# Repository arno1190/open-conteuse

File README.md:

# Galia

Two current custom handheld designs and an original bilingual listening collection. **Engineering RFQ release: physical validation and integrated audio firmware remain pending. No hardware is offered for sale.**

- **Galia Mini (contact ID):** 65 × 95 × 24 mm; a keyed cartridge selects audio stored inside the player, with an adult-replaceable picture behind a clear window. Passive DS2401 serial ID, two wear contacts, no NFC or audio on the card. Cartridge protrudes 20 mm when seated.
- **Galia Explore:** 67 × 95 × 24 mm, 2.4-inch display and button navigation. USB-C charging/data and 3.5 mm headphones on both.
- **Parent studio:** existing local import, exact-revision approval, card assignment and export foundation. Never deployed publicly.

[French showcase](https://arno1190.github.io/open-conteuse/?lang=fr) · [English showcase](https://arno1190.github.io/open-conteuse/?lang=en) · [RFQ launch playbook](rfq/LAUNCH-PLAYBOOK.md) · [RFQ scope](rfq/README.md) · [Design/assembly dossier](docs/design/README.md)

The intended differentiator is parent-controlled, highly personal listening made with their chosen tools and authorised sources. [MCP and provider/TTS connections remain under assessment](docs/PERSONALIZATION.md); no subscription/API compatibility is claimed. [Control UX and tactile-cap design](docs/design/UX.md) define the current refinement.

## Stories and cards

[Three original bilingual adventures](content/starter/README.md), [printable cards](content/starter/cards.pdf), [read-aloud booklet](content/starter/collection.pdf). Paper artwork does not activate the electronic reader. Scripts are editorial drafts; downloadable synthetic recordings and browser fallback are demonstrations, not approved final audio.

## Sources and checks

[Native KiCad](hardware/) · [OpenSCAD and prototype print meshes](enclosure/) · [BOM/cost assumptions](rfq/costs.json) · [Firmware](firmware/README.md) · [Independent audit](docs/AUDIT.md) · [Validation](docs/VALIDATION.md) · [Roadmap](docs/ROADMAP.md)

```sh
npm ci --ignore-scripts
sh scripts/check.sh
sh scripts/cad-check.sh
PIO=pio sh scripts/firmware-check.sh
python3 -m conteuse.studio --root .studio
```

Python host has no runtime dependencies. KiCad 9, OpenSCAD and PlatformIO are separate CAD/build requirements. The studio binds loopback and prints a per-launch token. Current firmware diagnostics keep audio muted; codec playback, hardware transfer and physical validation are unfinished.

Only the current designs are kept on main; earlier iterations remain in Git history. Original host/CAD/docs MIT; firmware GPL-3.0-or-later; original starter stories/art CC0-1.0. Dependencies retain upstream licences. No proprietary story libraries are included.

[Card exploded view and Wi-Fi administration](docs/design/CARDS.md): source-implemented parent setup/transfer/assignment and replaceable printed pictures; physical device and audio playback qualification remain pending.

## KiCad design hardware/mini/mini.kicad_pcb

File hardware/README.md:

# Current hardware

Only current RFQ designs are present. Open each folder's same-name .kicad_pro in KiCad9. All dimensions are nominal; physical validation pending.

- mini/:65×95×24mm contact-ID player main board,4layers60×83×1.2mm.
- explore/:67×95×24mm display player main board, same board envelope.
- card-reader/:50×11×1.6mm, protected single-drop1-Wire reader,2layers.
- story-card/:20×12×0.8mm DS2401P+ passive ROM token,2layers, selective hardgold wear pads.

Every folder includes exact-identity/reference BOM with source and search link, native schematic/PCB, parts data and actual checks. Drawing-defined parts still require supplier approval. [Dossier/assembly](../docs/design/README.md), [electrical notes](../docs/design/ELECTRICAL.md), [RFQ](../rfq/README.md).

Native KiCad upstream footprint geometry retains its library licence/exception; see LICENSES.md in board folders. Generated original CAD is MIT. No fabrication approval is implied.

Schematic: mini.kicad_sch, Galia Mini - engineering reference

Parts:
C1, C2, C3, C7, C16, C20, C26, C29: GRM21BR61A106KE19L; C_0805_2012Metric
C4, C5, C6: GRM21BR61A226ME44L; C_0805_2012Metric
C8, C11, C12, C13, C14, C15, C19, C21, C22, C23, C25, C30: GRM188R71C104KA01D; C_0603_1608Metric
C9, C10, C24: GRM188R61A105KA61D; C_0603_1608Metric
C17, C18: GRM32ER60J107ME20L; C_1210_3225Metric
D1: LTST-C190KGKT; LED_0603_1608Metric
H1, H2, H3, H4: M2; MountingHole_2.2mm_M2
J1: USB4105-GF-A; USB_C_Receptacle_GCT_USB4105-xx-A_16P_TopMnt_Horizontal
J2: DM3D-SF; microSD_HC_Hirose_DM3D-SF
J3: SJ-43514-SMT-TR; SJ43514
J4, J5, J6: S2B-PH-SM4-TB; JST_PH_S2B-PH-SM4-TB_1x02-1MP_P2.00mm_Horizontal
J7: BM07B-SRSS-TB; JST_SH_BM07B-SRSS-TB_1x07-1MP_P1.00mm_Vertical
L1: XFL4020-152MEC; L_Coilcraft_XxL4020
Q1: MMBT3904LT1G; SOT-23
R1: RC0603FR-071K78L; R_0603_1608Metric
R2: RC0603FR-073K57L; R_0603_1608Metric
R3: RC0603FR-073K01L; R_0603_1608Metric
R4, R7, R10, R13: RC0603FR-07100KL; R_0603_1608Metric
R5, R14, R15: RC0603FR-072K2L; R_0603_1608Metric
R6, R8, R9, R11, R16, R17, R22, R25, R26, R30, R31, R32, R33, R34, R35, R36, R37: RC0603FR-0710KL; R_0603_1608Metric
R12: RC0603FR-0720KL; R_0603_1608Metric
R18, R19: RC0603FR-075K1L; R_0603_1608Metric
R20, R21: RC0603FR-0727RL; R_0603_1608Metric
R23: RC0603JR-070RL; R_0603_1608Metric
R24: RC0603FR-071KL; R_0603_1608Metric
R45: RT0603BRD071ML; R_0603_1608Metric
R46: RT0603BRD07187KL; R_0603_1608Metric
SW1, SW2, SW3, SW4, SW5, SW10, SW11: KMR221GLFS; SW_Push_1P1T_NO_CK_KMR2
SW9: JS102011SAQN; SW_SPDT_CK_JS102011SAQN
TP1: GND; TestPoint_Pad_D1.0mm
TP2: 3V2; TestPoint_Pad_D1.0mm
TP3: UART_TX; TestPoint_Pad_D1.0mm
TP4: UART_RX; TestPoint_Pad_D1.0mm
TP5: MUTED; TestPoint_Pad_D1.0mm
TP6: IO6; TestPoint_Pad_D1.0mm
TP7: IO7; TestPoint_Pad_D1.0mm
TP8: SYS; TestPoint_Pad_D1.0mm
TP9: BAT; TestPoint_Pad_D1.0mm
TP10: 1V8; TestPoint_Pad_D1.0mm
U1: ESP32-S3-WROOM-1-N16R8; ESP32-S3-WROOM-1-R1
U2: BQ24074RGTR; VQFN-16-1EP_3x3mm_P0.5mm_EP1.6x1.6mm
U3: TPS63020DSJR; TPS63020_DSJ
U4: TLV75518PDBVR; SOT-23-5
U5: TLV320DAC3100IRHBR; Texas_RHB0032E_VQFN-32-1EP_5x5mm_P0.5mm_EP3.45x3.45mm
U6: SN74LVC1G74DCUR; VSSOP-8_2.3x2mm_P0.5mm
U7: SN74LVC1G08DBVR; SOT-23-5
U8: MAX98357AETE+T; TQFN-16-1EP_3x3mm_P0.5mm_EP1.23x1.23mm
U9: TCA9534PWR; TSSOP-16_4.4x5mm_P0.65mm
U10: USBLC6-2SC6; SOT-23-6

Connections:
/1V8: C10.1, C11.1, TP10.1, U4.5 (OUT), U5.3 (DVDD)
/3V2: C4.1, C5.1, C6.1, C9.1, C12.1, C13.1, C14.1, C15.1, C16.1, C21.1, C22.1, C23.1, C25.1, C26.1, C29.1, C30.1, J2.4, J7.1, R8.1, R9.1, R14.1, R15.1, R16.1, R17.1, R22.1, R25.1, R26.1, R30.1, R31.1, R32.1, R33.1, R34.1, R35.1, R36.1, R37.1, R45.1, TP2.1, U1.2 (3V3), U3.4 (VOUT), U3.5 (VOUT), U4.1 (IN), U4.3 (EN), U5.2 (IOVDD), U5.17 (AVDD), U5.21 (SPKVDD), U5.24 (SPKVDD), U5.28 (HPVDD), U6.8 (VCC), U7.5 (VCC), U9.16 (VCC)
/AMP_GAIN: R13.1, U8.2 (GAIN_SLOT)
/AMP_SD: R11.2, R12.1, U8.4 (~SD_MODE)
/BAT: C3.1, J5.1, TP9.1, U2.2 (BAT), U2.3 (BAT)
/BOOT_N: R17.2, SW10.1, U1.27 (IO0)
/CC1: J1.A5, R18.1
/CC2: J1.B5, R19.1
/CELL_NTC: J6.1, U2.1 (TS)
/CHG_ILIM: R1.1, U2.12 (ILIM)
/CHG_ISET: R2.1, U2.16 (ISET)
/CHG_ITERM: R3.1, U2.15 (ITERM)
/CODEC_IRQ: R6.1, U1.23 (IO21), U5.32 (GPIO1)
/GND: C1.2, C2.2, C3.2, C4.2, C5.2, C6.2, C7.2, C8.2, C9.2, C10.2, C11.2, C12.2, C13.2, C14.2, C15.2, C16.2, C19.2, C20.2, C21.2, C22.2, C23.2, C24.2, C25.2, C26.2, C29.2, C30.2, J1.A1, J1.A12, J1.B1, J1.B12, J1.S1, J2.6, J2.9, J2.10, J2.11, J3.4 (RING2_GND), J5.2, J6.2, J7.2, Q1.2, R1.2, R2.2, R3.2, R4.2, R7.2, R10.2, R12.2, R18.2, R19.2, R24.2, R46.2, SW1.2, SW2.2, SW3.2, SW4.2, SW5.2, SW9.3, SW10.2, SW11.2, TP1.1, U1.1 (GND), U1.40 (GND), U1.41 (GND), U2.4 (~CE), U2.5 (EN2), U2.8 (VSS), U2.17 (VSS), U3.2 (GND), U3.15 (PGND_EP), U4.2 (GND), U5.1 (IOVSS), U5.8 (MCLK), U5.16 (AVSS), U5.18 (DVSS), U5.20 (SPKVSS), U5.25 (SPKVSS), U5.29 (HPVSS), U5.33 (EP), U6.1 (CLK), U6.2 (D), U6.4 (GND), U7.3 (GND), U8.3 (GND), U8.11 (GND), U8.15 (GND), U8.17 (PAD), U9.1 (A0), U9.2 (A1), U9.3 (A2), U9.8 (GND), U10.2 (GND)
/HPL: C17.1, U5.27 (HPL)
/HPR: C18.1, U5.30 (HPR)
/HP_L: C17.2, J3.2 (TIP_L)
/HP_R: C18.2, J3.3 (RING1_R)
/I2C_SCL: R15.2, U1.38 (IO2), U5.10 (SCL), U9.14 (SCL)
/I2C_SDA: R14.2, U1.39 (IO1), U5.9 (SDA), U9.15 (SDA)
/I2S_BCLK: U1.33 (IO40), U5.7 (BCLK), U8.16 (BCLK)
/I2S_DATA: U1.35 (IO42), U5.5 (DIN), U8.1 (DIN)
/I2S_LRCLK: U1.34 (IO41), U5.6 (WCLK), U8.14 (LRCLK)
/IO4: U1.4 (IO4), U5.31 (RESET_N)
/IO5: R9.2, U1.5 (IO5), U6.6 (CLR_N)
/IO6: R23.2, TP6.1, U1.6 (IO6)
/IO7: TP7.1, U1.7 (IO7)
/IO8: J7.6, R25.2, U1.12 (IO8)
/IRQ_BASE: Q1.1, R6.2, R7.1
/KEY_A: R31.2, SW2.1, U9.5 (P1)
/KEY_B: R35.2, U9.10 (P5)
/KEY_DOWN: R32.2, U9.6 (P2)
/KEY_LEFT: R33.2, SW1.1, U9.7 (P3)
/KEY_RIGHT: R34.2, SW3.1, U9.9 (P4)
/KEY_UP: R30.2, U9.4 (P0)
/KEY_VOL_DOWN: R36.2, SW4.1, U9.11 (P6)
/KEY_VOL_UP: R37.2, SW5.1, U9.12 (P7)
/LATCH_ALLOW: U6.3 (Q_N), U7.1 (A)
/LED_K: D1.1, R24.1
/LED_STATUS: D1.2, U1.25 (IO48)
/MCU_EN: C24.1, R16.2, SW11.1, U1.3 (EN)
/MICBIAS: R5.1, U5.12 (MICBIAS)
/MICDET: J3.1 (SLEEVE_MICDET), R5.2, U5.11 (VOL_MICDET)
/MUTED: R23.1, TP5.1, U6.5 (Q)
/MUTE_PRE_N: Q1.3, R8.2, U6.7 (PRE_N)
/PWR_EN: R4.1, SW9.2, U3.12 (EN)
/REG_FB: R45.2, R46.1, U3.3 (FB)
/SD_CS: J2.2, R22.2, U1.18 (IO10)
/SPI_MISO: J2.7, U1.21 (IO13)
/SPI_MOSI: J2.3, U1.19 (IO11)
/SPI_SCK: J2.5, U1.20 (IO12)
/SPK_GATE: R11.1, U7.4 (Y)
/SPK_N: J4.2, U8.10 (OUTN)
/SPK_P: J4.1, U8.9 (OUTP)
/SPK_REQUEST: R10.1, U1.24 (IO47), U7.2 (B)
/SW_L1: L1.1, U3.8 (L1), U3.9 (L1)
/SW_L2: L1.2, U3.6 (L2), U3.7 (L2)
/SYS: C2.1, C7.1, C19.1, C20.1, R13.2, SW9.1, TP8.1, U2.10 (OUT), U2.11 (OUT), U3.10 (VIN), U3.11 (VIN), U3.13 (PS_SYNC), U8.7 (VDD), U8.8 (VDD)
/UART_RX: TP4.1, U1.36 (RXD0)
/UART_TX: TP3.1, U1.37 (TXD0)
/USB_DN: R21.2, U1.13 (USB_D-)
/USB_DP: R20.2, U1.14 (USB_D+)
/USB_N: J1.A7, J1.B7, R21.1, U10.3 (IO2), U10.4 (IO2)
/USB_P: J1.A6, J1.B6, R20.1, U10.1 (IO1), U10.6 (IO1)
/VBUS: C1.1, J1.A4, J1.A9, J1.B4, J1.B9, U2.6 (EN1), U2.13 (IN), U10.5 (VBUS)
/VINA: C8.1, U3.1 (VINA_internal)

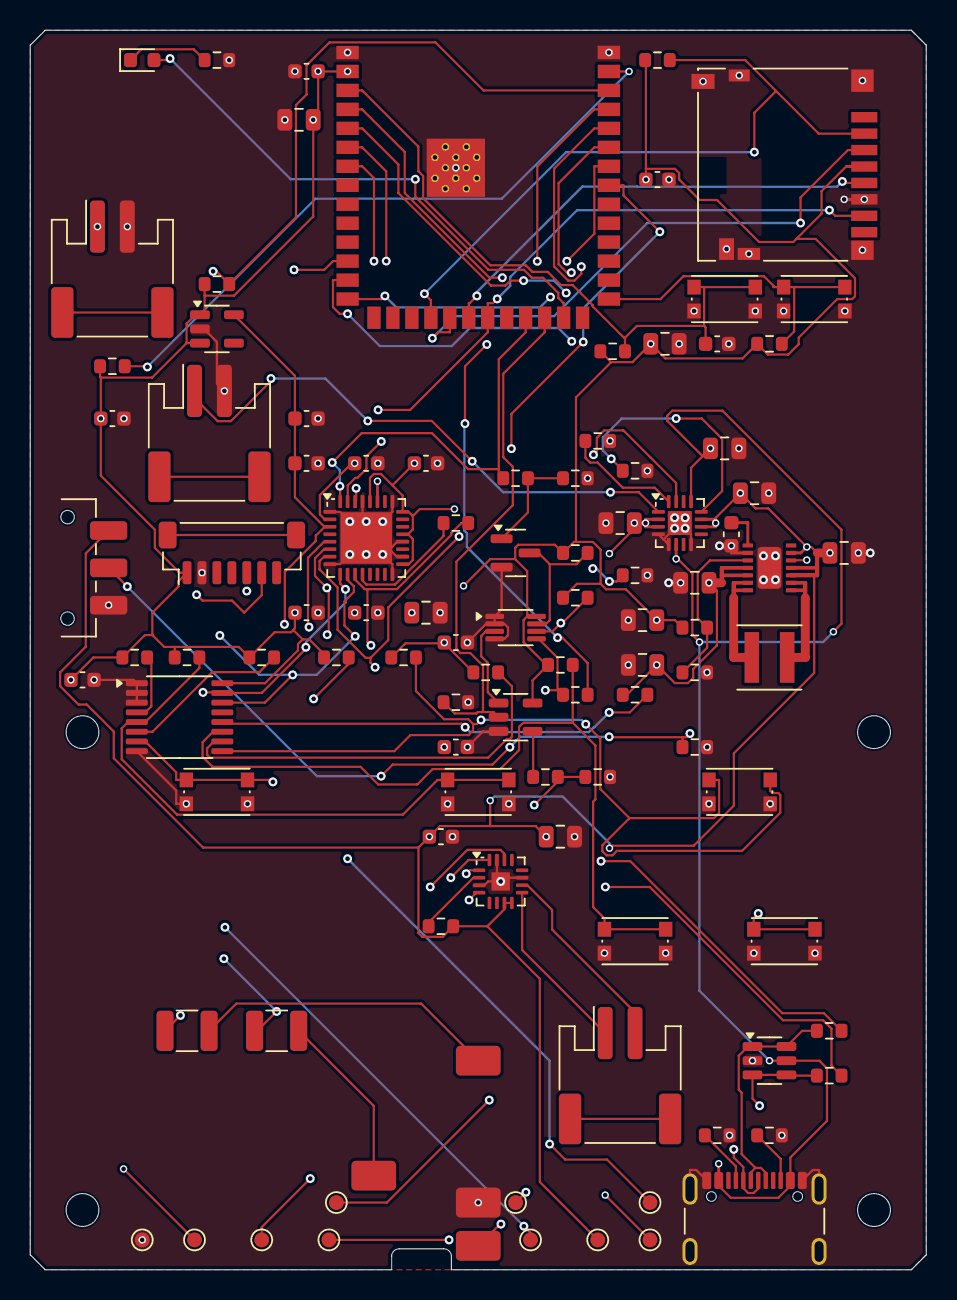
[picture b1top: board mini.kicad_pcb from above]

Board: 4 copper layers, 60.0 x 83.0 mm, 104 parts (0 on the bottom side), 66 nets.

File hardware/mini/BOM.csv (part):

reference,mpn,description,quantity,unit_eur_low,unit_eur_high,source,footprint,basis,search
U1,ESP32-S3-WROOM-1-N16R8,mcu,1,3.8,6.8,https://www.espressif.com/sites/default/files/documentation/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,Compact:ESP32-S3-WROOM-1-R1,planning allowance; not supplier quote,https://www.digikey.fr/en/products?keywords=ESP32-S3-WROOM-1-N16R8
U2,BQ24074RGTR,power,1,1.5,3,https://www.ti.com/lit/ds/symlink/bq24074.pdf,Package_DFN_QFN:VQFN-16-1EP_3x3mm_P0.5mm_EP1.6x1.6mm,planning allowance; not supplier quote,https://www.digikey.fr/en/products?keywords=BQ24074RGTR
R1,RC0603FR-071K78L,power,1,0.01,0.06,https://www.yageo.com/en/Product/Index/product_type/chip-resistors,Resistor_SMD:R_0603_1608Metric,planning allowance; not supplier quote,https://www.digikey.fr/en/products?keywords=RC0603FR-071K78L
R2,RC0603FR-073K57L,power,1,0.01,0.06,https://www.yageo.com/en/Product/Index/product_type/chip-resistors,Resistor_SMD:R_0603_1608Metric,planning allowance; not supplier quote,https://www.digikey.fr/en/products?keywords=RC0603FR-073K57L
R3,RC0603FR-073K01L,power,1,0.01,0.06,https://www.yageo.com/en/Product/Index/product_type/chip-resistors,Resistor_SMD:R_0603_1608Metric,planning allowance; not supplier quote,https://www.digikey.fr/en/products?keywords=RC0603FR-073K01L
C1,GRM21BR61A106KE19L,power,1,0.06,0.2,https://www.murata.com/en-global/products/capacitor/mlcc,Capacitor_SMD:C_0805_2012Metric,planning allowance; not supplier quote,https://www.digikey.fr/en/products?keywords=GRM21BR61A106KE19L
C2,GRM21BR61A106KE19L,power,1,0.06,0.2,https://www.murata.com/en-global/products/capacitor/mlcc,Capacitor_SMD:C_0805_2012Metric,planning allowance; not supplier quote,https://www.digikey.fr/en/products?keywords=GRM21BR61A106KE19L
C3,GRM21BR61A106KE19L,power,1,0.06,0.2,https://www.murata.com/en-global/products/capacitor/mlcc,Capacitor_SMD:C_0805_2012Metric,planning allowance; not supplier quote,https://www.digikey.fr/en/products?keywords=GRM21BR61A106KE19L
U3,TPS63020DSJR,power,1,2.2,4.5,https://www.ti.com/lit/ds/symlink/tps63020.pdf,Compact:TPS63020_DSJ,planning allowance; not supplier quote,https://www.digikey.fr/en/products?keywords=TPS63020DSJR
L1,XFL4020-152MEC,power,1,0.9,1.8,https://www.coilcraft.com/en-us/products/power/shielded-indu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,Inductor_SMD:L_Coilcraft_XxL4020,planning allowance; not supplier quote,https://www.digikey.fr/en/products?keywords=XFL4020-152MEC
C4,GRM21BR61A226ME44L,power,1,0.12,0.35,https://www.murata.com/en-global/products/capacitor/mlcc,Capacitor_SMD:C_0805_2012Metric,planning allowance; not supplier quote,https://www.digikey.fr/en/products?keywords=GRM21BR61A226ME44L
C5,GRM21BR61A226ME44L,power,1,0.12,0.35,https://www.murata.com/en-global/products/capacitor/mlcc,Capacitor_SMD:C_0805_2012Metric,planning allowance; not supplier quote,https://www.digikey.fr/en/products?keywords=GRM21BR61A226ME44L
C6,GRM21BR61A226ME44L,power,1,0.12,0.35,https://www.murata.com/en-global/products/capacitor/mlcc,Capacitor_SMD:C_0805_2012Metric,planning allowance; not supplier quote,https://www.digikey.fr/en/products?keywords=GRM21BR61A226ME44L
R45,RT0603BRD071ML,power,1,0.08,0.3,https://www.yageo.com/en/Product/Index/product_type/chip-resistors,Resistor_SMD:R_0603_1608Metric,planning allowance; not supplier quote,https://www.digikey.fr/en/products?keywords=RT0603BRD071ML
R46,RT0603BRD07187KL,power,1,0.08,0.3,https://www.yageo.com/en/Product/Index/product_type/chip-resistors,Resistor_SMD:R_0603_1608Metric,planning allowance; not supplier quote,https://www.digikey.fr/en/products?keywords=RT0603BRD07187KL
C7,GRM21BR61A106KE19L,power,1,0.06,0.2,https://www.murata.com/en-global/products/capacitor/mlcc,Capacitor_SMD:C_0805_2012Metric,planning allowance; not supplier quote,https://www.digikey.fr/en/products?keywords=GRM21BR61A106KE19L
C8,GRM188R71C104KA01D,power,1,0.02,0.08,https://www.murata.com/en-global/products/capacitor/mlcc,Capacitor_SMD:C_0603_1608Metric,planning allowance; not supplier quote,https://www.digikey.fr/en/products?keywords=GRM188R71C104KA01D
R4,RC0603FR-07100KL,power,1,0.01,0.06,https://www.yageo.com/en/Product/Index/product_type/chip-resistors,Resistor_SMD:R_0603_1608Metric,planning allowance; not supplier quote,https://www.digikey.fr/en/products?keywords=RC0603FR-07100KL
SW9,JS102011SAQN,power,1,0.5,1.5,https://www.ckswitches.com/media/1422/js.pdf,Button_Switch_SMD:SW_SPDT_CK_JS102011SAQN,planning allowance; not supplier quote,https://www.digikey.fr/en/products?keywords=JS102011SAQN
U4,TLV75518PDBVR,audio,1,0.2,0.7,https://www.ti.com/lit/ds/symlink/tlv755p.pdf,Package_TO_SOT_SMD:SOT-23-5,planning allowance; not supplier quote,https://www.digikey.fr/en/products?keywords=TLV75518PDBVR
C9,GRM188R61A105KA61D,audio,1,0.03,0.12,https://www.murata.com/en-global/products/capacitor/mlcc,Capacitor_SMD:C_0603_1608Metric,planning allowance; not supplier quote,https://www.digikey.fr/en/products?keywords=GRM188R61A105KA61D
C10,GRM188R61A105KA61D,audio,1,0.03,0.12,https://www.murata.com/en-global/products/capacitor/mlcc,Capacitor_SMD:C_0603_1608Metric,planning allowance; not supplier quote,https://www.digikey.fr/en/products?keywords=GRM188R61A105KA61D
U5,TLV320DAC3100IRHBR,audio,1,2,4,https://www.ti.com/lit/ds/symlink/tlv320dac3100.pdf,Package_DFN_QFN:Texas_RHB0032E_VQFN-32-1EP_5x5mm_P0.5mm_EP3.45x3.45mm,planning allowance; not supplier quote,https://www.digikey.fr/en/products?keywords=TLV320DAC3100IRHBR
C11,GRM188R71C104KA01D,audio,1,0.02,0.08,https://www.murata.com/en-global/products/capacitor/mlcc,Capacitor_SMD:C_0603_1608Metric,planning allowance; not supplier quote,https://www.digikey.fr/en/products?keywords=GRM188R71C104KA01D
C12,GRM188R71C104KA01D,audio,1,0.02,0.08,https://www.murata.com/en-global/products/capacitor/mlcc,Capacitor_SMD:C_0603_1608Metric,planning allowance; not supplier quote,https://www.digikey.fr/en/products?keywords=GRM188R71C104KA01D
C13,GRM188R71C104KA01D,audio,1,0.02,0.08,https://www.murata.com/en-global/products/capacitor/mlcc,Capacitor_SMD:C_0603_1608Metric,planning allowance; not supplier quote,https://www.digikey.fr/en/products?keywords=GRM188R71C104KA01D
C14,GRM188R71C104KA01D,audio,1,0.02,0.08,https://www.murata.com/en-global/products/capacitor/mlcc,Capacitor_SMD:C_0603_1608Metric,planning allowance; not supplier quote,https://www.digikey.fr/en/products?keywords=GRM188R71C104KA01D
C15,GRM188R71C104KA01D,audio,1,0.02,0.08,https://www.murata.com/en-global/products/capacitor/mlcc,Capacitor_SMD:C_0603_1608Metric,planning allowance; not supplier quote,https://www.digikey.fr/en/products?keywords=GRM188R71C104KA01D
C16,GRM21BR61A106KE19L,audio,1,0.06,0.2,https://www.murata.com/en-global/products/capacitor/mlcc,Capacitor_SMD:C_0805_2012Metric,planning allowance; not supplier quote,https://www.digikey.fr/en/products?keywords=GRM21BR61A106KE19L
R5,RC0603FR-072K2L,audio,1,0.01,0.06,https://www.yageo.com/en/Product/Index/product_type/chip-resistors,Resistor_SMD:R_0603_1608Metric,planning allowance; not supplier quote,https://www.digikey.fr/en/products?keywords=RC0603FR-072K2L
C17,GRM32ER60J107ME20L,audio,1,0.5,1.2,https://www.murata.com/en-global/products/capacitor/mlcc,Capacitor_SMD:C_1210_3225Metric,planning allowance; not supplier quote,https://www.digikey.fr/en/products?keywords=GRM32ER60J107ME20L
C18,GRM32ER60J107ME20L,audio,1,0.5,1.2,https://www.murata.com/en-global/products/capacitor/mlcc,Capacitor_SMD:C_1210_3225Metric,planning allowance; not supplier quote,https://www.digikey.fr/en/products?keywords=GRM32ER60J107ME20L
J3,SJ-43514-SMT-TR,audio,1,0.8,2,https://jp.sameskydevices.com/product/resource/sj-4351x-smt.pdf,Compact:SJ43514,planning allowance; not supplier quote,https://www.digikey.fr/en/products?keywords=SJ-43514-SMT-TR
U6,SN74LVC1G74DCUR,audio,1,0.25,0.7,https://www.ti.com/lit/ds/symlink/sn74lvc1g74.pdf,Package_SO:VSSOP-8_2.3x2mm_P0.5mm,planning allowance; not supplier quote,https://www.digikey.fr/en/products?keywords=SN74LVC1G74DCUR
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
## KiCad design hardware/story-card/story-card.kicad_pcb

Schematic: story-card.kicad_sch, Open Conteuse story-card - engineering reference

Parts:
H1, H2: M1.6; Mount_M1_6
J1: OC-ID-CONTACTS; ContactPads_Bottom
U1: DS2401P+; TSOC-6_3.76x3.94mm_P1.27mm

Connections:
/CARD_DQ: J1.2, U1.2 (DQ)
/GND: J1.1, U1.1 (GND)

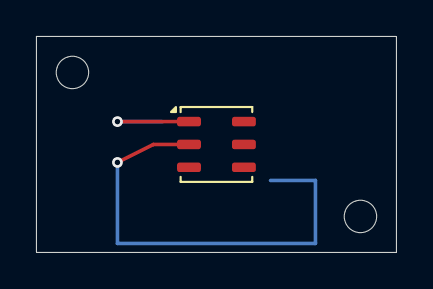
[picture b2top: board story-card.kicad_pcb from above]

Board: 2 copper layers, 20.0 x 12.0 mm, 4 parts (0 on the bottom side), 2 nets.

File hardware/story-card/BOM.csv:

reference,mpn,description,quantity,unit_eur_low,unit_eur_high,source,footprint,basis,search
U1,DS2401P+,card,1,3.65,5,https://www.analog.com/media/en/technical-documentation/data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,Package_SO_J-Lead:TSOC-6_3.76x3.94mm_P1.27mm,planning allowance; not supplier quote,https://www.digikey.fr/en/products?keywords=DS2401P%2B
J1,OC-ID-CONTACTS,card,1,0,0,selective hard-gold contact drawing; no audio storage,Compact:ContactPads_Bottom,planning allowance; not supplier quote,https://www.digikey.fr/en/products?keywords=OC-ID-CONTACTS
CASE,OC-ID-CARD-CASE,Two printed cartridge halves and label; no audio storage,1,0.5,2,enclosure/card.scad,external,engineering allowance; not a quote,https://www.google.com/search?q=OC-ID-CARD-CASE
SCR,ISO7045-Z-M1.6x3-A2,Two cartridge handle panhead screws,2,0.04,0.15,docs/design/README.md,external,engineering allowance; not a quote,https://www.google.com/search?q=ISO7045-Z-M1.6x3-A2
PCB,OC-ID-CARD-PCB,20x12x0.8mm 2layer selective hardgold wear pads; MOQ/NRE excluded,1,1,4,hardware/story-card/story-card.kicad_pcb,external,engineering allowance; not a quote,https://www.google.com/search?q=OC-ID-CARD-PCB

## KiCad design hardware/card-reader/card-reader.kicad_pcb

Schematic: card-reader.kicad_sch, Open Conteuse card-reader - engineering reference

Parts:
D1: TPD1E10B06DPYR; Texas_DPY0002A_0.6x1mm_P0.65mm
D2: BAT54S,215; SOT-23
H1, H2: M1.6; Mount_M1_6
J1: OC-WIRE-3; Wire3_Top
P1, P2: P70-1000045R; Pogo_P70_1000045
R1: RC0603FR-074K3L; R_0603_1608Metric
R2: RC0603FR-07330RL; R_0603_1608Metric

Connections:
/3V2: D2.2, J1.1, R1.1
/CARD_DQ: D1.1, P2.1, R2.2
/GND: D1.2, D2.1, J1.2, P1.1
/IO8: D2.3, J1.3, R1.2, R2.1

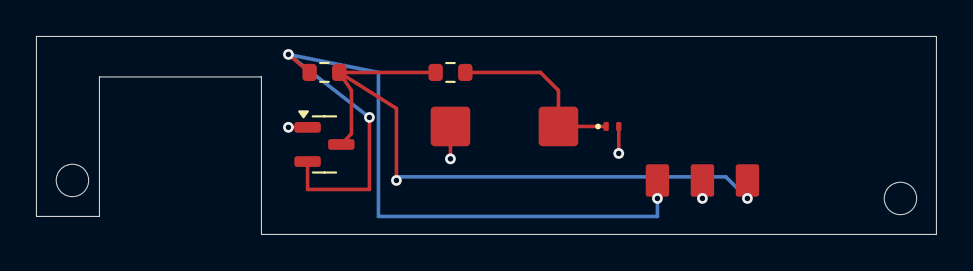
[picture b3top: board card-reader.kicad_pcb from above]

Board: 2 copper layers, 50.0 x 11.0 mm, 9 parts (0 on the bottom side), 4 nets.

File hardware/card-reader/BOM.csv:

reference,mpn,description,quantity,unit_eur_low,unit_eur_high,source,footprint,basis,search
J1,OC-WIRE-3,card,1,0,0,drawing-defined solder-wire termination,Compact:Wire3_Top,planning allowance; not supplier quote,https://www.digikey.fr/en/products?keywords=OC-WIRE-3
P1,P70-1000045R,card,1,0.8,1.8,https://www.harwin.com/products/P70-1000045R,Compact:Pogo_P70_1000045,planning allowance; not supplier quote,https://www.digikey.fr/en/products?keywords=P70-1000045R
P2,P70-1000045R,card,1,0.8,1.8,https://www.harwin.com/products/P70-1000045R,Compact:Pogo_P70_1000045,planning allowance; not supplier quote,https://www.digikey.fr/en/products?keywords=P70-1000045R
R1,RC0603FR-074K3L,card,1,0.01,0.06,https://www.yageo.com/en/Product/Index/product_type/chip-resistors,Resistor_SMD:R_0603_1608Metric,planning allowance; not supplier quote,https://www.digikey.fr/en/products?keywords=RC0603FR-074K3L
R2,RC0603FR-07330RL,card,1,0.01,0.06,https://www.yageo.com/en/Product/Index/product_type/chip-resistors,Resistor_SMD:R_0603_1608Metric,planning allowance; not supplier quote,https://www.digikey.fr/en/products?keywords=RC0603FR-07330RL
D1,TPD1E10B06DPYR,card,1,0.15,0.5,https://www.ti.com/lit/ds/symlink/tpd1e10b06.pdf,Package_SON:Texas_DPY0002A_0.6x1mm_P0.65mm,planning allowance; not supplier quote,https://www.digikey.fr/en/products?keywords=TPD1E10B06DPYR
D2,"BAT54S,215",card,1,0.05,0.2,https://assets.nexperia.com/documents/data-sheet/BAT54_SER.pdf,Package_TO_SOT_SMD:SOT-23,planning allowance; not supplier quote,https://www.digikey.fr/en/products?keywords=BAT54S%2C215
PCB,OC-ID-READER-PCB,50x11x1.6mm 2layer FR4 reader; MOQ/NRE excluded,1,1,3,hardware/card-reader/card-reader.kicad_pcb,external,engineering allowance; not a quote,https://www.google.com/search?q=OC-ID-READER-PCB

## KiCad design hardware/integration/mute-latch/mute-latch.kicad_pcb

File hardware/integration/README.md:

# Integrated modular prototype — revision 1

This is the detailed successor to the original bench envelope. The configuration is inspired by the owner's canteen project workflow: one catalogue, one placement file, sourcing queries on every BOM row, native CAD references and reproducible export checks. No private reference-project material is included.

**Status: nominal CAD prototype, not a physically validated or procurement-complete product.** Downloadable prototype STLs are in `../../enclosure/integrated/print/`. Do not substitute the historical `enclosure/shell.scad` for this enclosure. The integrated case is 112 × 210 × 50 mm. The Mini uses the actual long PN532 board; Explore omits NFC and uses the 2090 display.

## Sources and exact configuration

- [BOM.csv](BOM.csv): exact manufacturer/order identifiers, per-device quantities, observed supplier price/stock and DigiKey, Mouser and AliExpress search queries for **every** row. Search results are discovery links, not approved substitutes or authenticity guarantees.
- [catalog.json](catalog.json): dimensions, supplier CAD source URLs, Git object identities, source/derived hashes, mounting-hole coordinates, dimensional conflicts, quotes and assumptions.
- [layout.json](layout.json): all module poses, ports and removable-card/wire corridors in mm.
- [status.json](status.json): generated missing-quote/availability gates and minimum purchase-pack subtotals for one Mini plus one Explore.
- [mute-latch](mute-latch): native routed KiCad 9 schematic/PCB and local libraries for the independent insertion-mute latch. Existing controls PCB remains `../controls`.

Selected modules: Espressif ESP32-S3-DevKitC-1-N16R8 **PCB V1.1**; Adafruit 364 PN532 v1.6 (Mini), 2090 ILI9341 capacitive TFT (Explore; touch unused), 4682 microSD, 6309 TLV320DAC3100 headphone DAC, 3006 MAX98357A speaker amplifier, 6091 BQ25185 charger, 328 protected cell, 3351 enclosed speaker, 805 slide switch; Pololu 2873 regulated 3.3 V supply. Small-part MPNs are enumerated separately, rather than hiding them in an allowance.

No substitute board is dimensionally equivalent merely because it uses the same IC. PN532 manufacturer CAD is 120 × 50 mm whereas retail prose differs. The protected cell reservation combines the larger published dimension on each axis. The speaker uses the larger 19.7 mm CAD depth. ESP assembled/header height is a **14.5 mm reservation**, not a measured height. Switch STEP is an undetailed rectangular envelope: actuator location/slot and cradle require actual-part measurements. Neither uncertain item is represented as a detailed exact model.

## Electrical integration contract

Protected battery → BQ25185 BAT; charger LOAD → regulator VIN and MAX98357A VIN. Pololu fixed 3.3 V → MCU 3V3 and all logic modules; common GND. Charger retains factory 4.2 V / 1 A configuration (cell specified max charge 1.2 A). Slide switch pulls regulator EN to GND to sleep; never drive EN high. Raw LOAD remains powered when regulator sleeps; this is not a service isolation switch. Regulator typical near-battery output is 1.5 A, startup around 700 mA until regulation: delay Wi-Fi/heavy loads. Actual concurrent current, startup, thermal and brownout tests remain pending.

**Never connect MCU native USB/5V while it receives external 3V3.** Charging USB-C is charge-only. Service flashing requires disconnecting external power and confirming isolation; EN-off alone is insufficient. Do not attach charger/battery before polarity and short-circuit checks. Use the battery's manufacturer protection; the printed cage does not provide electrical protection.

Integrated wiring target (not yet implemented in firmware): buttons GPIO4/5/6/7/15/16/17/18; I²C SDA1/SCL2; PN532 IRQ8/RESET9; SD CS10/MOSI11/SCK12/MISO13; TFT CS14/DC48, RESET tied to ESP EN; I²S BCLK40/LRCLK41/DATA42; amplifier request47; latch Q21 and active-low CLR39. Reserve GPIO38 for DevKit V1.1 RGB, USB19/20, OPI35/36/37, boot straps0/3/45/46 and UART43/44. The old bench profile uses different GPIOs and lacks the TLV320 codec driver: **do not flash it onto this wiring**. Integrated firmware/codec bring-up is an explicit release gate.

Mute latch: TLV320 IO1 IRQ pulse drives 2N3904 through10k; base100k to GND; collector pulls HC74 PRE_N low (10k pullup). HC74 Q→GPIO21; /Q AND GPIO47 via HC08→amp SD. D/CLK grounded, CLR_N GPIO39 with10k pullup; all unused gate inputs tied, unused outputs NC. GPIO47 and SD each have10k pulldown; add the mandatory extra **local10k at amp SD/GND** so an unplugged harness leaves it muted. Both logic ICs use regulated3V3 and100nF decoupling. See schematic for header pin order; never infer order from this prose.

Boot holds GPIO47 LOW. Configure codec headset detection/internal oscillator and repeating IRQ, clear checked codec flags, clear latch with amplifier held LOW, release CLR, then perform checked no-headset/status and Q-low reads before enabling. I²C failure means muted. PRE and CLR simultaneous LOW can make both Q and /Q HIGH: never enable while clearing. This circuit latches insertion IRQ even if the loop stalls, but is not protection against codec reset, lost AVDD or broken IRQ. No physical headphone-mute safety result is claimed.

## Adult assembly and validation

1. Confirm every received PCB revision/MPN, battery polarity, exact connector and fastener geometry. Measure MCU assembled height, switch actuator, solder/header protrusions and actual plug barrels. Update catalogue/poses and rerun exports before a full case print.
2. Print the coupon first. Confirm M2.5 screw clearance, plain DIN934 nut capture and connector opening clearances. Nyloc nuts are taller and are not substitutes.
3. PETG baseline: 0.4 mm nozzle, 0.2 mm layers, ≥3 perimeters, 20–30% infill. These are starting settings, not validated strength. Slicer/orientation/support review is required; no printer-specific G-code is supplied. Front exterior faces the bed; all STL exports have nonnegative Z. Wide flat parts may need a brim; tall wall ledges may need support.
4. Install nuts into front pockets. Insert button stems **from inside**: the large internal head retains each cap. Fit controls PCB over them, then test free travel before wiring. Fit variant PCB and sealed speaker using the rigid4 mm PETG spacer; it is not an acoustic gasket.
5. Assemble removable carrier, modules, battery cage and cover. Use two MCU bars, one regulator bar and one switch bar. Route trimmed soldered harnesses with strain relief; avoid exposed plug-in jumpers. Leave SD extraction corridor clear. Do not overtighten against PCBs or pouch cell. Tie tension must close on the rigid cage, not compress the cell.
6. Verify service access and that lid/retainers cannot touch components or wires. Use M2.5×6 socket screws and plain2 mm-high nuts; selected mounting count43 pairs/device includes4 case,4 carrier,12 front,15 rear module,4 MCU,2 regulator,2 switch pairs. Verify screw engagement before tightening: supplier PCB stack variations require rechecking length.
7. Bench test isolated USB logic first with current limiting; then power rail startup/load, SD/NFC/TFT, codec/I²S and insertion mute. Finally battery/charge thermal, sound level, runtime, acoustic seal, NFC range, drop/retention and repeated assembly tests. Record results; all remain pending.

The render/export/mesh checks prove only properties of digital geometry. They do not establish electrical safety, child suitability, battery containment, mechanical strength or that every actual part fits. No purchases or fabrication orders were made.

## Reproduce

```sh
python3 scripts/integrated_hardware.py
python3 scripts/export_integrated.py
sh scripts/check.sh
sh scripts/cad-check.sh
sh scripts/firmware-check.sh
```

KiCad9 and OpenSCAD2021.01 are the checked CAD tool versions. Generator `scripts/generate_mute_latch.py` requires system Python with pcbnew. Preview rendering additionally uses the pinned numpy/matplotlib packages in `scripts/requirements-preview.txt`. The catalogue and geometric host checks need only Python standard library.

### Screw and solder clearance assumptions

M2.5×6 is measured under its head. For1.57/1.6mm modulePCBs, the tip lies4.43/4.4mm below the PCB support plane; global blind bores preserve a nominal0.6mm floor skin instead of being refilled by the case/carrier union. Speaker body is raised to6.4mm with a4mm spacer. Native CAD flange bearing surfaces are localZ1.0–2.7mm (1.7mm thick), so posts end at globalZ7.4 and screw tips atZ3.1. Verify the actual flange before assembly. Its post bores remain blind and nut cavities are open from the PCB side. Screw heads and tool approach still require received-part verification. Trim through-hole solder leads to≤2mm under every3mm PCB standoff; do not leave long header tails to touch the carrier. Bare standoffs do not provide insulation for unknown protruding components.

CAD poses use bare module assemblies without optional tall pin headers or the MAX98357A screw-terminal block. Solder the strain-relieved speaker lead directly to the amplifier output pads; do not add an unmodelled terminal block. Battery's included matching JST-PH lead connects to charger BAT; retain its protection and verify polarity. Any added plug/socket, terminal block or replacement speaker lead requires an exact BOM row, envelope and revised fit check. Latch's specified Samtec headers are included in its10mm upper reservation and still require received-part/lead-trim checks.

## Full visual atlas

The [combined visual design document](../../docs/visual-atlas) includes exterior/orthographic, exploded, sectional, module and service views for Mini and Explore, with a downloadable PDF. Its orange faces show sections of the supplied CAD solids; they do not reveal hidden speaker/cell construction. Shared-module close-ups are grouped with Mini; Explore adds its display and eight-switch controls view. Visual proxies and generic component bodies are labelled and do not replace received-part measurements.

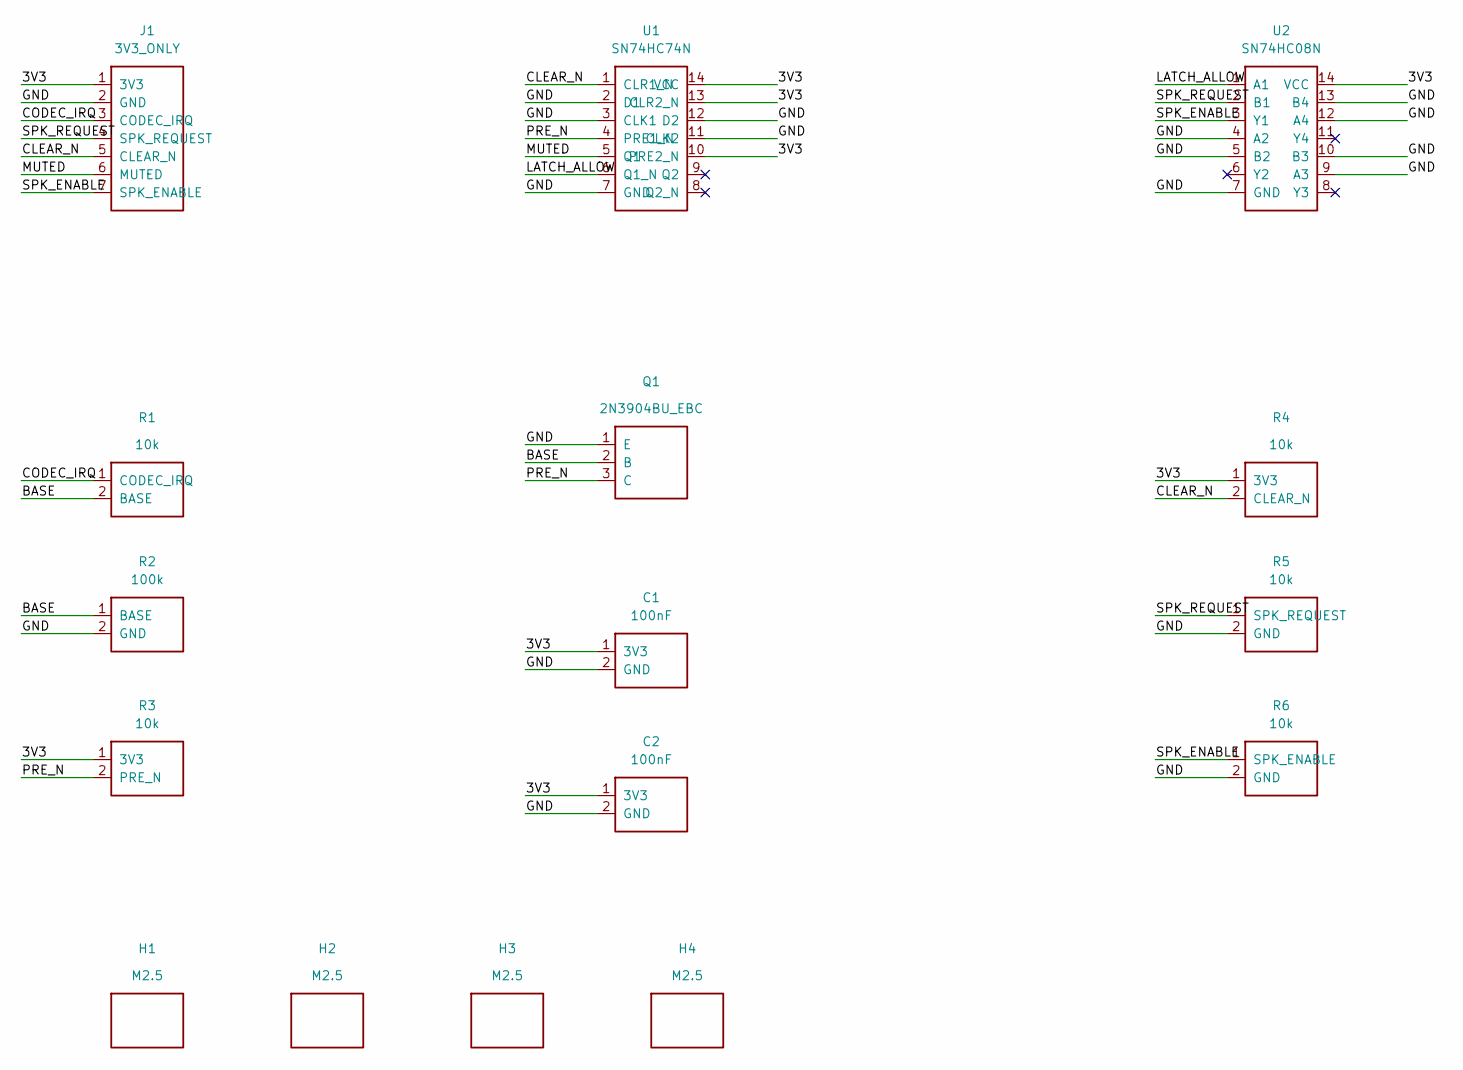
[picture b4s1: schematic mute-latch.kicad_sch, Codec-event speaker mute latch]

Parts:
C1, C2: 100nF; C_Disc_D5.0mm_W2.5mm_P2.54mm
H1, H2, H3, H4: M2.5; MountingHole_2.7mm_M2.5
J1: 3V3_ONLY; PinHeader_1x07_P2.54mm_Vertical
Q1: 2N3904BU_EBC; TO-92_Inline
R1, R3, R4, R5, R6: 10k; R_Axial_DIN0207_L6.3mm_D2.5mm_P7.62mm_Horizontal
R2: 100k; R_Axial_DIN0207_L6.3mm_D2.5mm_P7.62mm_Horizontal
U1: SN74HC74N; DIP-14_W7.62mm
U2: SN74HC08N; DIP-14_W7.62mm

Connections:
/3V3: C1.1 (3V3), C2.1 (3V3), J1.1 (3V3), R3.1 (3V3), R4.1 (3V3), U1.10 (PRE2_N), U1.13 (CLR2_N), U1.14 (VCC), U2.14 (VCC)
/BASE: Q1.2 (B), R1.2 (BASE), R2.1 (BASE)
/CLEAR_N: J1.5 (CLEAR_N), R4.2 (CLEAR_N), U1.1 (CLR1_N)
/CODEC_IRQ: J1.3 (CODEC_IRQ), R1.1 (CODEC_IRQ)
/GND: C1.2 (GND), C2.2 (GND), J1.2 (GND), Q1.1 (E), R2.2 (GND), R5.2 (GND), R6.2 (GND), U1.2 (D1), U1.3 (CLK1), U1.7 (GND), U1.11 (CLK2), U1.12 (D2), U2.4 (A2), U2.5 (B2), U2.7 (GND), U2.9 (A3), U2.10 (B3), U2.12 (A4), U2.13 (B4)
/LATCH_ALLOW: U1.6 (Q1_N), U2.1 (A1)
/MUTED: J1.6 (MUTED), U1.5 (Q1)
/PRE_N: Q1.3 (C), R3.2 (PRE_N), U1.4 (PRE1_N)
/SPK_ENABLE: J1.7 (SPK_ENABLE), R6.1 (SPK_ENABLE), U2.3 (Y1)
/SPK_REQUEST: J1.4 (SPK_REQUEST), R5.1 (SPK_REQUEST), U2.2 (B1)

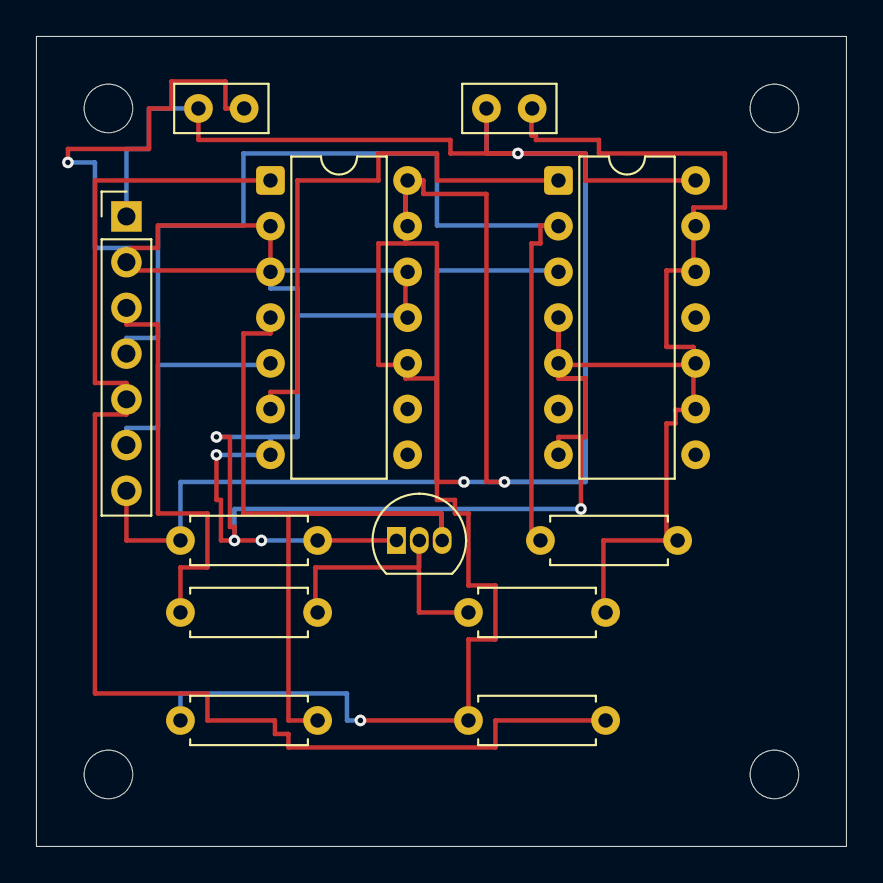
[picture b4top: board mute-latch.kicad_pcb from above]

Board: 2 copper layers, 45.0 x 45.0 mm, 16 parts (0 on the bottom side), 10 nets.

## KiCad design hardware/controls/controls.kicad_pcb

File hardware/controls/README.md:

# Controls PCB v0.1

Native KiCad 9 schematic, project, local symbols and **fully routed** two-layer PCB. Scope: eight normally-open GPIO-to-ground switches, 1×9 harness and four mounting holes. This is the common Mini/Explore control daughterboard, **not a complete power/audio carrier**. Mini leaves three switches unpopulated. See ../PINOUT.md, ../BOM.csv and ../ASSEMBLY.md.

The schematic and PCB share deterministic symbol identities and net assignments. `scripts/generate_controls.py` generates the design using Debian `/usr/bin/python3` with pcbnew/KiCad 9; the routing algorithm is deterministic in geometry, while KiCad may assign fresh object UUIDs. The committed native sources are the review baseline. No copper fill is needed: ground is an explicit routed tree, and traces/vias obey project minima. Do not treat the switch net name RIGHT_B as a second B button; J1.5 is right/next and J1.6 is back/B (variant labels are listed in PINOUT.md).

```sh
# Optional regeneration; no need to regenerate simply to check the files.
XDG_CONFIG_HOME="$PWD/work/config" XDG_CACHE_HOME="$PWD/work/cache" XDG_DATA_HOME="$PWD/work/data" /usr/bin/python3 scripts/generate_controls.py
sh scripts/cad-check.sh
```

The check includes all warnings, no exclusions, and schematic/PCB parity. Reports saved in `work/cad`; the checked release snapshot is in `hardware/reports`. No Gerber/fabrication order is generated or submitted.

Footprints are embedded from KiCad 9 libraries (https://www.kicad.org/libraries/license/, CC-BY-SA-4.0 with the KiCad library exception). Original circuit, symbols, layout generation and documentation are MIT. Preserve upstream footprint/library notices and exception when reusing library data; the exception permits ordinary PCB design distribution.

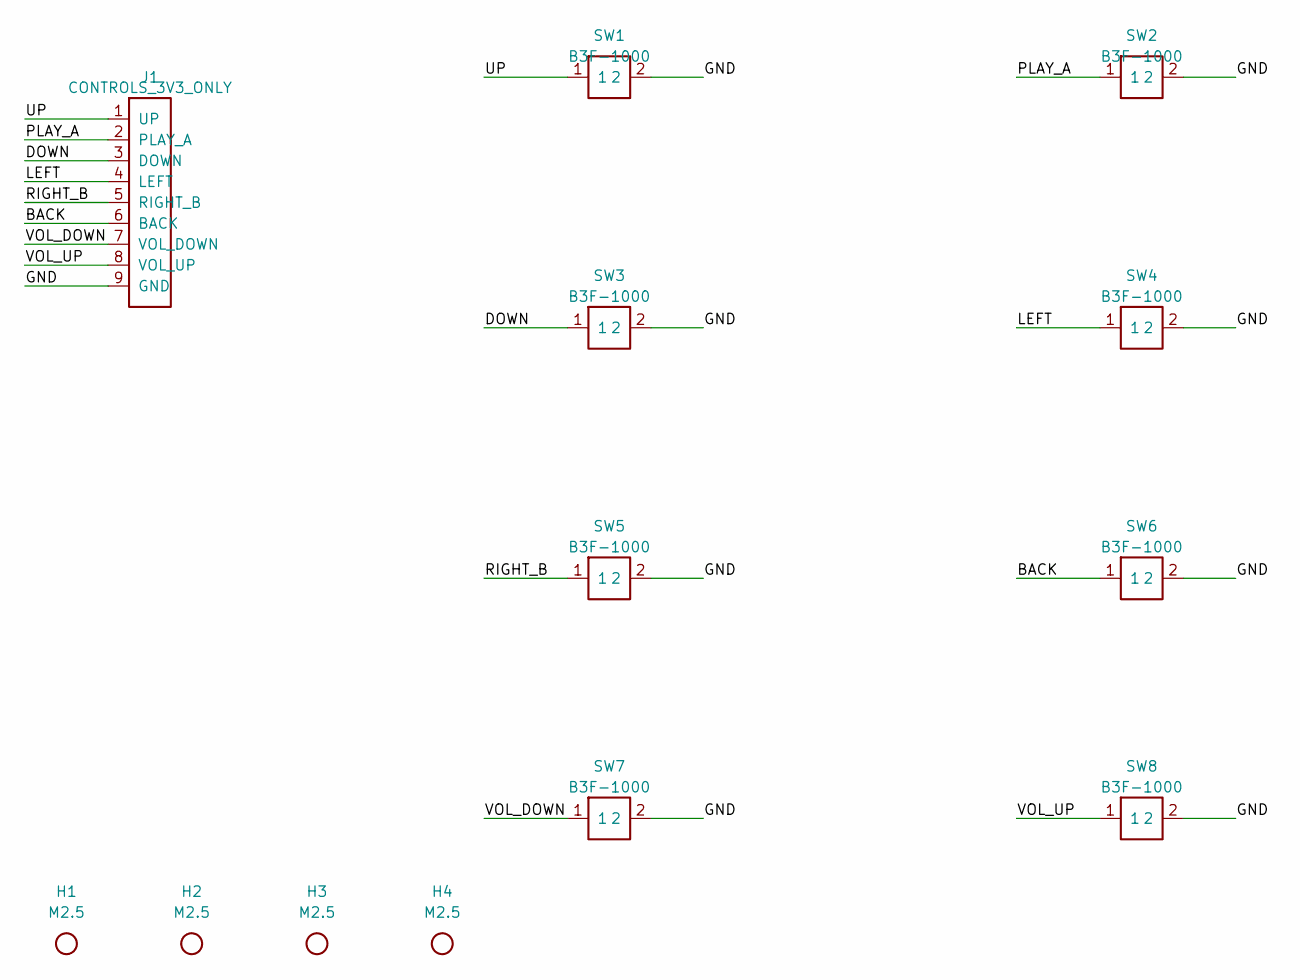
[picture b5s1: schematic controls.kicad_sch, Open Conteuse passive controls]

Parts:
H1, H2, H3, H4: M2.5; MountingHole_2.7mm_M2.5
J1: CONTROLS_3V3_ONLY; PinHeader_1x09_P2.54mm_Vertical
SW1, SW2, SW3, SW4, SW5, SW6, SW7, SW8: B3F-1000; SW_PUSH_6mm

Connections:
/BACK: J1.6 (BACK), SW6.1
/DOWN: J1.3 (DOWN), SW3.1
/GND: J1.9 (GND), SW1.2, SW2.2, SW3.2, SW4.2, SW5.2, SW6.2, SW7.2, SW8.2
/LEFT: J1.4 (LEFT), SW4.1
/PLAY_A: J1.2 (PLAY_A), SW2.1
/RIGHT_B: J1.5 (RIGHT_B), SW5.1
/UP: J1.1 (UP), SW1.1
/VOL_DOWN: J1.7 (VOL_DOWN), SW7.1
/VOL_UP: J1.8 (VOL_UP), SW8.1
